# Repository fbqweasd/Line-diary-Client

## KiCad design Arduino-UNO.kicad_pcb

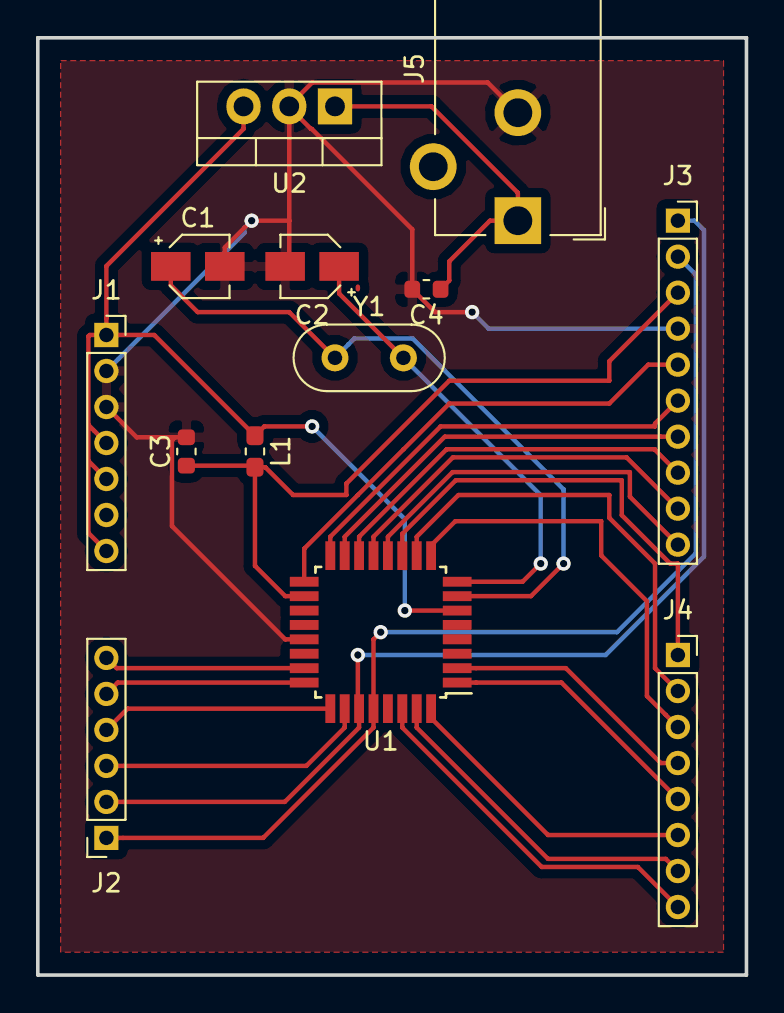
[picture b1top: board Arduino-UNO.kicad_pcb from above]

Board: 2 copper layers, 39.4 x 52.1 mm, 13 parts (0 on the bottom side), 26 nets.

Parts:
C1, C2: CP1; CP_Elec_3x5.4
C3: 1uF; C_0603_1608Metric
C4: 0.1uF; C_0603_1608Metric
J1: Conn_01x07; PinSocket_1x07_P2.00mm_Vertical
J2: Conn_01x06; PinSocket_1x06_P2.00mm_Vertical
J3: Conn_01x10; PinSocket_1x10_P2.00mm_Vertical
J4: Conn_01x08; PinSocket_1x08_P2.00mm_Vertical
J5: POWER_Barrel; BarrelJack_CUI_PJ-102AH_Horizontal
L1: L; L_0603_1608Metric_Pad1.05x0.95mm_HandSolder
U1: ATmega328P-AU; TQFP-32_7x7mm_P0.8mm
U2: LM7805_TO220; TO-220-3_Vertical
Y1: 8MHz / 16MHz; Crystal_HC52-6mm_Vertical

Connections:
A0: J2.6, U1.23
A1: J2.5, U1.24
A2: J2.4, U1.25
A3: J2.3, U1.26
A4: J2.2, J3.1, U1.27
A5: J2.1, J3.2, U1.28
AREF: C3.1, J3.3, L1.2, U1.18, U1.20
D0: J4.8, U1.30
D1: J4.7, U1.31
D2: J4.6, U1.32
D3: J4.5, U1.1
D4: J4.4, U1.2
D5: J4.3, U1.9
D6: J4.2, U1.10
D7: J4.1, U1.11
D8: J3.10, U1.12
D9: J3.9, U1.13
D10: J3.8, U1.14
D11: J3.7, U1.15
D12: J3.6, U1.16
D13: J3.5, U1.17
GND: C1.2, C2.2, C3.2, C4.2, J1.2, J1.3, J3.4, J5.2, U1.3, U1.5, U1.21, U2.2
unnamed: C4.1, J5.1, U2.1
VCC: J1.1, J1.4, J1.7, J1.VCC, L1.1, U1.4, U1.6, U2.3
XTAL1: C1.1, U1.7, Y1.1
XTAL2: C2.1, U1.8, Y1.2

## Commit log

2018-11-23 README
